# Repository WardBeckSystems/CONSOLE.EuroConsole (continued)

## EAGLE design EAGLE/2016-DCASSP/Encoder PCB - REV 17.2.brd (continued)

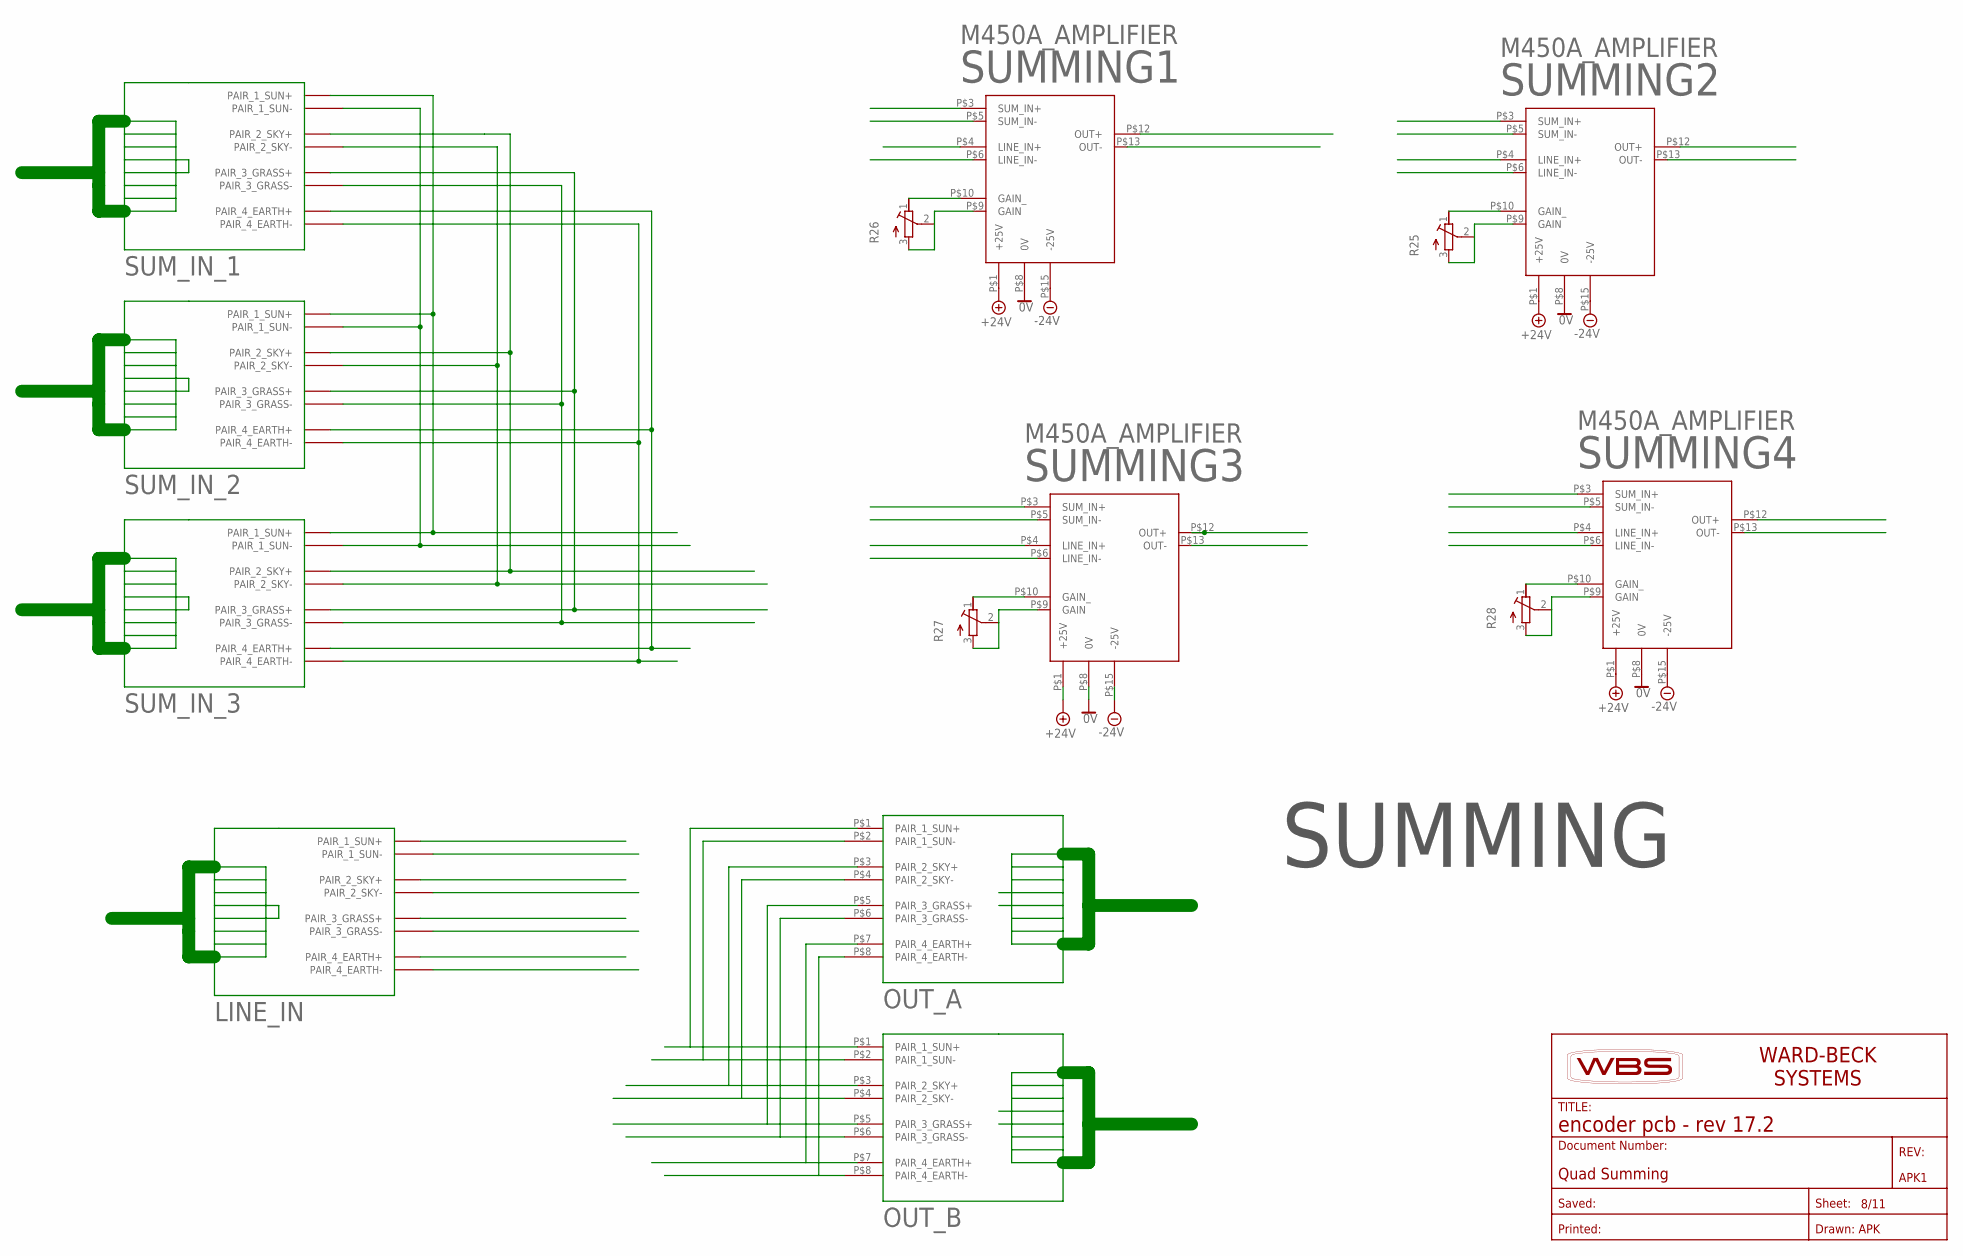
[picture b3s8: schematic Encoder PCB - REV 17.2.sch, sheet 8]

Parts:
APK1: Quad Summing; WBS-FRAME_PCB
LINE_IN: QTP-OUT; PLACEHOLDER
OUT_A: QTP-IN; PLACEHOLDER
OUT_B: QTP-IN; PLACEHOLDER
R25, R26, R27, R28: R-TRIMM43P; RTRIM43P
SUMMING1, SUMMING2, SUMMING3, SUMMING4: M450A_AMPLIFIER
SUM_IN_1, SUM_IN_2, SUM_IN_3: QTP-OUT; PLACEHOLDER

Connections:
0V: SUMMING1.P$8 (0V), SUMMING2.P$8 (0V), SUMMING3.P$8 (0V), SUMMING4.P$8 (0V)
+24V: SUMMING1.P$1 (+25V), SUMMING2.P$1 (+25V), SUMMING3.P$1 (+25V), SUMMING4.P$1 (+25V)
-24V: SUMMING1.P$15 (-25V), SUMMING2.P$15 (-25V), SUMMING3.P$15 (-25V), SUMMING4.P$15 (-25V)
unnamed: SUM_IN_1.P$1 (PAIR_1_SUN+), SUM_IN_1.P$5 (PAIR_3_GRASS+), SUM_IN_1.P$7 (PAIR_4_EARTH+), SUM_IN_2.P$1 (PAIR_1_SUN+), SUM_IN_2.P$3 (PAIR_2_SKY+), SUM_IN_2.P$5 (PAIR_3_GRASS+), SUM_IN_2.P$7 (PAIR_4_EARTH+), SUM_IN_3.P$1 (PAIR_1_SUN+), SUM_IN_3.P$3 (PAIR_2_SKY+), SUM_IN_3.P$5 (PAIR_3_GRASS+), SUM_IN_3.P$7 (PAIR_4_EARTH+)
unnamed: SUM_IN_1.P$2 (PAIR_1_SUN-), SUM_IN_1.P$6 (PAIR_3_GRASS-), SUM_IN_1.P$8 (PAIR_4_EARTH-), SUM_IN_2.P$2 (PAIR_1_SUN-), SUM_IN_2.P$6 (PAIR_3_GRASS-), SUM_IN_2.P$8 (PAIR_4_EARTH-), SUM_IN_3.P$2 (PAIR_1_SUN-), SUM_IN_3.P$4 (PAIR_2_SKY-), SUM_IN_3.P$6 (PAIR_3_GRASS-), SUM_IN_3.P$8 (PAIR_4_EARTH-)
unnamed: SUM_IN_1.P$4 (PAIR_2_SKY-), SUM_IN_2.P$4 (PAIR_2_SKY-)
unnamed: OUT_A.P$8 (PAIR_4_EARTH-), OUT_B.P$8 (PAIR_4_EARTH-)
unnamed: OUT_A.P$4 (PAIR_2_SKY-), OUT_B.P$4 (PAIR_2_SKY-)
unnamed: OUT_A.P$2 (PAIR_1_SUN-), OUT_B.P$2 (PAIR_1_SUN-)
unnamed: OUT_A.P$1 (PAIR_1_SUN+), OUT_B.P$1 (PAIR_1_SUN+)
unnamed: OUT_A.P$3 (PAIR_2_SKY+), OUT_B.P$3 (PAIR_2_SKY+)
unnamed: OUT_A.P$5 (PAIR_3_GRASS+), OUT_B.P$5 (PAIR_3_GRASS+)
unnamed: OUT_A.P$7 (PAIR_4_EARTH+), OUT_B.P$7 (PAIR_4_EARTH+)
unnamed: OUT_A.P$6 (PAIR_3_GRASS-), OUT_B.P$6 (PAIR_3_GRASS-)
unnamed: R25.1 (E), SUMMING2.P$10 (GAIN_)
unnamed: R25.2 (S), R25.3 (A), SUMMING2.P$9 (GAIN)
unnamed: R26.1 (E), SUMMING1.P$10 (GAIN_)
unnamed: R26.2 (S), R26.3 (A), SUMMING1.P$9 (GAIN)
unnamed: R27.1 (E), SUMMING3.P$10 (GAIN_)
unnamed: R27.2 (S), R27.3 (A), SUMMING3.P$9 (GAIN)
unnamed: R28.1 (E), SUMMING4.P$10 (GAIN_)
unnamed: R28.2 (S), R28.3 (A), SUMMING4.P$9 (GAIN)
unnamed: LINE_IN.P$1 (PAIR_1_SUN+), LINE_IN.P$3 (PAIR_2_SKY+), LINE_IN.P$4 (PAIR_2_SKY-), LINE_IN.P$5 (PAIR_3_GRASS+), LINE_IN.P$6 (PAIR_3_GRASS-), LINE_IN.P$7 (PAIR_4_EARTH+), LINE_IN.P$8 (PAIR_4_EARTH-)

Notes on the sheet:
SUMMING

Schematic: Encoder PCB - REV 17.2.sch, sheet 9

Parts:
APK3: VU METER PANEL; WBS-FRAME_PCB
NEOPIXEL1: QTP-IN; PLACEHOLDER
U$7, U$8, U$9, U$10: VU_METER
VU_METER_INPUT: QTP-OUT; PLACEHOLDER

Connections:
unnamed: U$7.P$2, VU_METER_INPUT.P$1 (PAIR_1_SUN+)
unnamed: U$7.P$1, VU_METER_INPUT.P$2 (PAIR_1_SUN-)
unnamed: U$8.P$2, VU_METER_INPUT.P$3 (PAIR_2_SKY+)
unnamed: U$8.P$1, VU_METER_INPUT.P$4 (PAIR_2_SKY-)
unnamed: U$10.P$1, VU_METER_INPUT.P$8 (PAIR_4_EARTH-)
unnamed: U$10.P$2, VU_METER_INPUT.P$7 (PAIR_4_EARTH+)
unnamed: U$9.P$2, VU_METER_INPUT.P$5 (PAIR_3_GRASS+)
unnamed: U$9.P$1, VU_METER_INPUT.P$6 (PAIR_3_GRASS-)
NEO_0V: NEOPIXEL1.P$3 (PAIR_2_SKY+), NEOPIXEL1.P$4 (PAIR_2_SKY-)
NEO_5V: NEOPIXEL1.P$1 (PAIR_1_SUN+), NEOPIXEL1.P$2 (PAIR_1_SUN-)

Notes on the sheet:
VU METERS

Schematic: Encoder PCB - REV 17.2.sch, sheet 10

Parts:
JP1, JP2: PINHD-1X8; 1X08
U3: DS1808Z-050+; SOIC127P600X175-16N
WBS8: DS1882 Adapter; WBS-FRAME_PCB

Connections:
unnamed: JP1.1, U3.1 (GND)
unnamed: JP1.2, U3.2 (A2)
unnamed: JP1.3, U3.3 (A1)
unnamed: JP1.4, U3.4 (VB)
unnamed: JP1.5, U3.5 (A0)
unnamed: JP1.6, U3.6 (W0)
unnamed: JP1.7, U3.7 (L0)
unnamed: JP1.8, U3.8 (H0)
unnamed: JP2.1, U3.9 (L1)
unnamed: JP2.2, U3.10 (H1)
unnamed: JP2.3, U3.11 (W)
unnamed: JP2.4, U3.12 (~CE)
unnamed: JP2.5, U3.13 (SDA)
unnamed: JP2.6, U3.14 (SCL)
unnamed: JP2.7, U3.15 (VCC)
unnamed: JP2.8, U3.16 (VDD)

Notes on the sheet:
DCP-Socket

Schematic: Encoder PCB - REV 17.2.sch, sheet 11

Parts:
BNC2: 1-227161-0; AMP_227161
C14: 100n/50v; C0805
EURO-BLOCK_2: CON-PHOENIX_RIGHT_ANGLE_3.81; CON-PHOENIX_MC1.5/3-G-3.81
G2: LSP10
GND-2: SJ
GROUND_POST: 22-23-2031
PAN_CON_2: 22-23-2031
QTP1, QTP2: CON-QTP; ASSMAN-RJ45
QTP_CENTER: CON-QTP; ASSMAN-RJ45
R201: 0R; R0805W
R202, R204: 37R5; R0805W
R203: 75R; R0805W
REARTH+: 0R; R0805W
REARTH-: 0R; R0805W
RGRASS+: 0R; R0805W
RGRASS-: 0R; R0805W
RSKY+: 0R; R0805W
RSKY-: 0R; R0805W
RSUN+: 0R; R0805W
RSUN-: 0R; R0805W
SJ_2: SJ
T2: XFMR_SCHOTT_61454; SCHOTT_61454
WBS9: QTP-BAC; WBS-FRAME_PCB
X2: 2514-; PAK100/2500-14
XLR2: CON-XLR-NEUTRIK_A_BISEXUAL; CON_NEUTRIK_A_BISEXUAL_H

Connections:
CH1+1: QTP1.P1+ (PAIR+1_SUN), QTP2.P1+ (PAIR+1_SUN), QTP_CENTER.P1+ (PAIR+1_SUN), RSUN+.1
CH1-1: QTP1.P1- (PAIR-1), QTP2.P1- (PAIR-1), QTP_CENTER.P1- (PAIR-1), RSUN-.1
CH2+1: EURO-BLOCK_2.+, PAN_CON_2.1, QTP1.P2+ (PAIR+2_SKY), QTP2.P2+ (PAIR+2_SKY), QTP_CENTER.P2+ (PAIR+2_SKY), RSKY+.1, T2.P5, XLR2.F2 (F2+), XLR2.M2 (M2+)
CH2-1: EURO-BLOCK_2.-, PAN_CON_2.2, QTP1.P2- (PAIR-2), QTP2.P2- (PAIR-2), QTP_CENTER.P2- (PAIR-2), RSKY-.1, T2.P8, XLR2.SHARED3 (S3-)
CH3+1: QTP1.P3+ (PAIR+3_GRASS), QTP2.P3+ (PAIR+3_GRASS), QTP_CENTER.P3+ (PAIR+3_GRASS), RGRASS+.1
CH3-1: QTP1.P3- (PAIR-3), QTP2.P3- (PAIR-3), QTP_CENTER.P3- (PAIR-3), RGRASS-.1
CH4+1: QTP1.P4+ (PAIR+4_EARTH), QTP2.P4+ (PAIR+4_EARTH), QTP_CENTER.P4+ (PAIR+4_EARTH), REARTH+.1
CH4-1: QTP1.P4- (PAIR-4), QTP2.P4- (PAIR-4), QTP_CENTER.P4- (PAIR-4), REARTH-.1
GND: GND-2.2, GROUND_POST.1, GROUND_POST.2, GROUND_POST.3, QTP1.P$9 (GROUND), QTP1.P$10 (GROUND), QTP1.P$11 (GROUND), QTP1.P$12 (GROUND), QTP2.P$9 (GROUND), QTP2.P$10 (GROUND), QTP2.P$11 (GROUND), QTP2.P$12 (GROUND), QTP_CENTER.P$9 (GROUND), QTP_CENTER.P$10 (GROUND), QTP_CENTER.P$11 (GROUND), QTP_CENTER.P$12 (GROUND), X2.3, X2.6, X2.9, X2.12; also elsewhere on the board
GND_PIN1_2: BNC2.2, C14.1, EURO-BLOCK_2.S, G2.MP, GND-2.1, PAN_CON_2.3, R203.2, T2.P4, T2.P6, XLR2.CHASSIS (GROUND), XLR2.F1, XLR2.GROUND, XLR2.M1
unnamed: R201.2, R204.2, T2.P1
unnamed: R202.2, R204.1, SJ_2.1
unnamed: BNC2.1, R201.1, R202.1
unnamed: C14.2, T2.P7
unnamed: R203.1, SJ_2.2
unnamed: RSUN+.2, X2.10
unnamed: REARTH-.2, X2.2
unnamed: REARTH+.2, X2.1
unnamed: RGRASS-.2, X2.5
unnamed: RGRASS+.2, X2.4
unnamed: RSKY-.2, X2.8
unnamed: RSKY+.2, X2.7
unnamed: RSUN-.2, X2.11

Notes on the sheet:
QTP-XLR

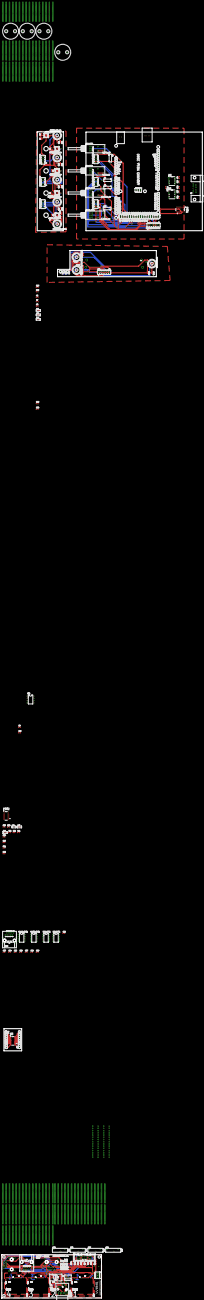
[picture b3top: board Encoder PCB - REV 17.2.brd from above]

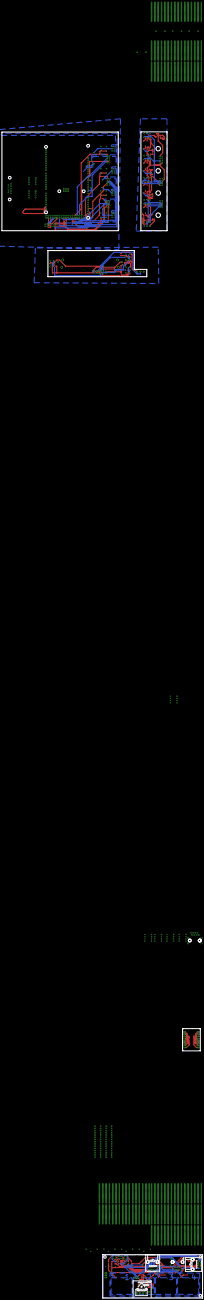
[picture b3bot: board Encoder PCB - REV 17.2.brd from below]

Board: 2 copper layers, 229.9 x 1336.6 mm, 214 parts (3 on the bottom side), 158 nets.

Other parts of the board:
U$5: C1-4-150731-094535
U$6: C2-5-150731-094535
U$11: C3-6-150731-094535
U$12: C4-7-150731-094535
U$13: GND_1-8-150731-094535
U$14: GND_2-9-150731-094535
U$15: GND_3-10-150731-094535
U$16: GND_4-11-150731-094535
U$17: GROUND_P-12-150731-094535
U$18: R101-17-150731-094535
U$19: R102-18-150731-094535
U$20: R103-19-150731-094535
U$21: R104-20-150731-094535
U$22: R201-21-150731-094535
U$23: R202-22-150731-094535
U$24: R203-23-150731-094535
U$25: R204-24-150731-094535
U$26: R301-25-150731-094535
U$27: R302-26-150731-094535
U$28: R303-27-150731-094535
U$29: R304-28-150731-094535
U$30: R401-29-150731-094535
U$31: R402-30-150731-094535
U$32: R403-31-150731-094535
U$33: R404-32-150731-094535
U$34: REARTH_-33-150731-094535
U$35: REARTH_-34-150731-094535
U$36: RGRASS_-35-150731-094535
U$37: RGRASS_-36-150731-094535
U$38: RSKY_-37-150731-094535
U$39: RSKY_-38-150731-094535
U$40: RSUN_-39-150731-094535
U$41: RSUN_-40-150731-094535
U$42: SJ_1-41-150731-094535
U$43: SJ_2-42-150731-094536
U$44: SJ_3-43-150731-094536
U$45: SJ_4-44-150731-094536
U$46: GND_PIN1_1; T1-45-150731-094536
U$47: GND_PIN1_2; T2-46-150731-094536
U$48: gnd; T3-47-150731-094536
U$49: gnd; T4-48-150731-094536

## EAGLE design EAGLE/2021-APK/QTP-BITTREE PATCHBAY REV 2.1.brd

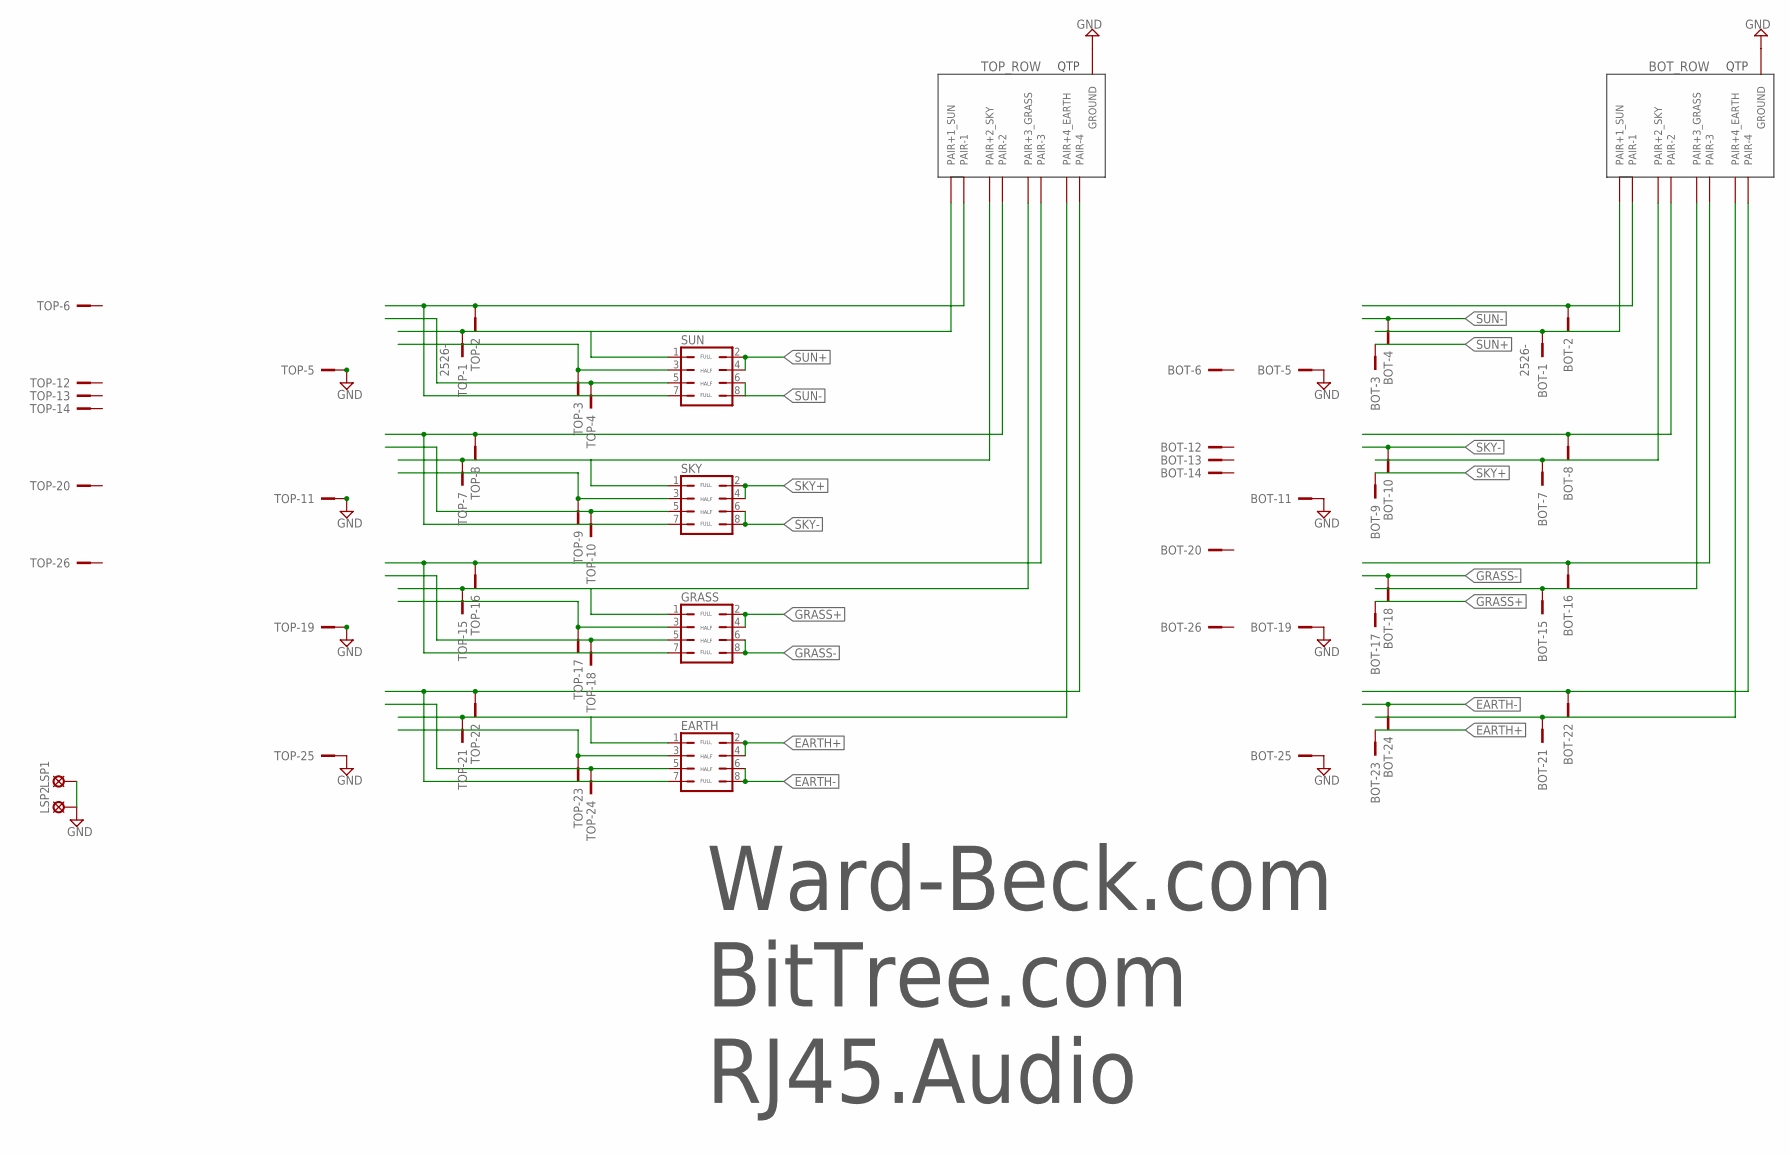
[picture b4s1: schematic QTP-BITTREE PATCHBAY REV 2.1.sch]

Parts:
BOT: 2526-; PAK100/2500-26
BOT_ROW: CON-QTP_VERT; ASSMAN-RJ45_VERT
EARTH: JP4Q
GRASS: JP4Q
LSP1, LSP2: LSP13
SKY: JP4Q
SUN: JP4Q
TOP: 2526-; PAK100/2500-26
TOP_ROW: CON-QTP_VERT; ASSMAN-RJ45_VERT

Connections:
EARTH+: BOT.23, EARTH.2, EARTH.4
EARTH-: BOT.24, EARTH.6, EARTH.8
GND: BOT.5, BOT.11, BOT.19, BOT.25, BOT_ROW.P$9 (GROUND), BOT_ROW.P$10 (GROUND), BOT_ROW.P$11 (GROUND), BOT_ROW.P$12 (GROUND), LSP1.MP, LSP2.MP, TOP.5, TOP.11, TOP.19, TOP.25, TOP_ROW.P$9 (GROUND), TOP_ROW.P$10 (GROUND), TOP_ROW.P$11 (GROUND), TOP_ROW.P$12 (GROUND)
GRASS+: BOT.17, GRASS.2, GRASS.4
GRASS-: BOT.18, GRASS.6, GRASS.8
unnamed: SUN.7, TOP.2, TOP_ROW.P$1 (PAIR-1)
unnamed: SKY.1, TOP.7, TOP_ROW.P$4 (PAIR+2_SKY)
unnamed: BOT.1, BOT_ROW.P$2 (PAIR+1_SUN)
unnamed: GRASS.1, TOP.15, TOP_ROW.P$6 (PAIR+3_GRASS)
unnamed: BOT.2, BOT_ROW.P$1 (PAIR-1)
unnamed: EARTH.1, TOP.21, TOP_ROW.P$8 (PAIR+4_EARTH)
unnamed: SUN.3, TOP.3
unnamed: SUN.5, TOP.4
unnamed: BOT.7, BOT_ROW.P$4 (PAIR+2_SKY)
unnamed: SKY.7, TOP.8, TOP_ROW.P$5 (PAIR-2)
unnamed: SKY.3, TOP.9
unnamed: SKY.5, TOP.10
unnamed: BOT.15, BOT_ROW.P$6 (PAIR+3_GRASS)
unnamed: GRASS.7, TOP.16, TOP_ROW.P$3 (PAIR-3)
unnamed: GRASS.3, TOP.17
unnamed: GRASS.5, TOP.18
unnamed: BOT.21, BOT_ROW.P$8 (PAIR+4_EARTH)
unnamed: EARTH.7, TOP.22, TOP_ROW.P$7 (PAIR-4)
unnamed: EARTH.3, TOP.23
unnamed: EARTH.5, TOP.24
unnamed: BOT.8, BOT_ROW.P$5 (PAIR-2)
unnamed: BOT.16, BOT_ROW.P$3 (PAIR-3)
unnamed: BOT.22, BOT_ROW.P$7 (PAIR-4)
SKY+: BOT.9, SKY.2, SKY.4
SKY-: BOT.10, SKY.6, SKY.8
SUN+: BOT.3, SUN.2, SUN.4
SUN-: BOT.4, SUN.6, SUN.8
TOP-P1: SUN.1, TOP.1, TOP_ROW.P$2 (PAIR+1_SUN)

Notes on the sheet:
FULL
HALF
Ward-Beck.com
BitTree.com RJ45.Audio

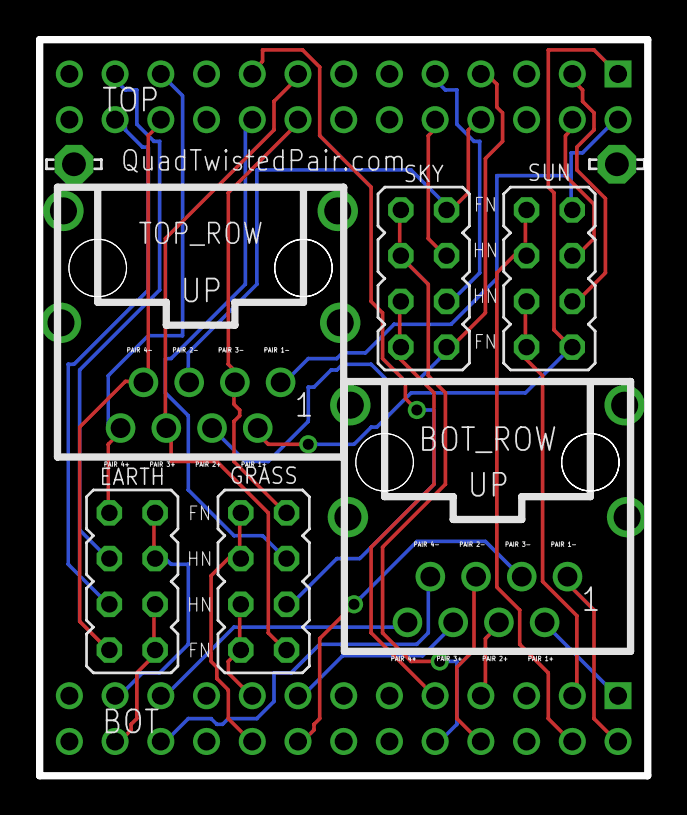
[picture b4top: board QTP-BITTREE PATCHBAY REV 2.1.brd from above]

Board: 2 copper layers, 33.8 x 40.9 mm, 10 parts (0 on the bottom side), 33 nets.

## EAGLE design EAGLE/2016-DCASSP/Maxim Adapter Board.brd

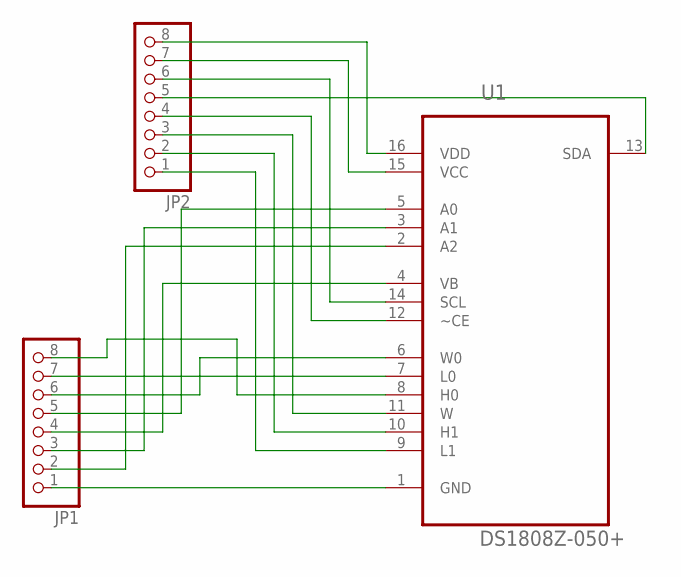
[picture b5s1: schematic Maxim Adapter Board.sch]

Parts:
JP1, JP2: PINHD-1X8; 1X08
U1: DS1808Z-050+; SOIC127P600X175-16N

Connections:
unnamed: JP1.1, U1.1 (GND)
unnamed: JP1.2, U1.2 (A2)
unnamed: JP1.3, U1.3 (A1)
unnamed: JP1.4, U1.4 (VB)
unnamed: JP1.5, U1.5 (A0)
unnamed: JP1.6, U1.6 (W0)
unnamed: JP1.7, U1.7 (L0)
unnamed: JP1.8, U1.8 (H0)
unnamed: JP2.1, U1.9 (L1)
unnamed: JP2.2, U1.10 (H1)
unnamed: JP2.3, U1.11 (W)
unnamed: JP2.4, U1.12 (~CE)
unnamed: JP2.5, U1.13 (SDA)
unnamed: JP2.6, U1.14 (SCL)
unnamed: JP2.7, U1.15 (VCC)
unnamed: JP2.8, U1.16 (VDD)

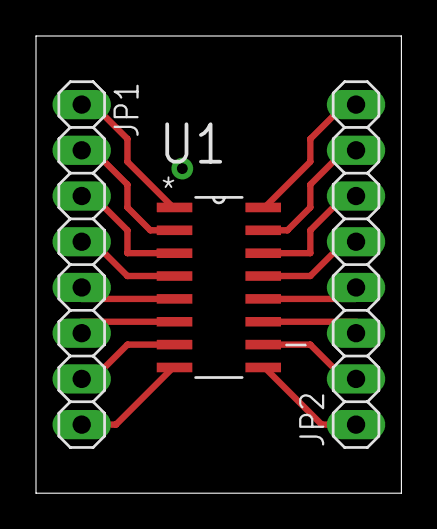
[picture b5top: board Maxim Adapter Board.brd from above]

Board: 2 copper layers, 20.3 x 25.4 mm, 3 parts (0 on the bottom side), 16 nets.

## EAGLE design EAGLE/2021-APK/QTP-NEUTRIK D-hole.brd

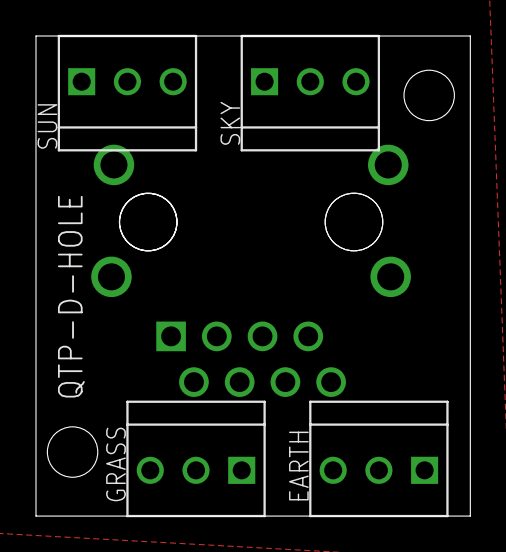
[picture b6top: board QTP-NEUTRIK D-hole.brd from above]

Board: 2 copper layers, 24.1 x 26.7 mm, 5 parts (1 on the bottom side), 9 nets, no tracks yet.

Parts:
EARTH: CON-WBS-LOCKING-0.1-3
GRASS: CON-WBS-LOCKING-0.1-3
SKY: CON-WBS-LOCKING-0.1-3
SUN: CON-WBS-LOCKING-0.1-3
U$1: CON-QTP_VERT; ASSMAN-RJ45_VERT

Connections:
GND: EARTH.P$3, GRASS.P$3, SKY.P$3, SUN.P$3, U$1.P$9, U$1.P$10, U$1.P$11, U$1.P$12
unnamed: SUN.P$1, U$1.P$2
unnamed: SUN.P$2, U$1.P$1
unnamed: SKY.P$1, U$1.P$4
unnamed: GRASS.P$1, U$1.P$6
unnamed: GRASS.P$2, U$1.P$3
unnamed: EARTH.P$1, U$1.P$8
unnamed: EARTH.P$2, U$1.P$7
SUN_N: SKY.P$2, U$1.P$5

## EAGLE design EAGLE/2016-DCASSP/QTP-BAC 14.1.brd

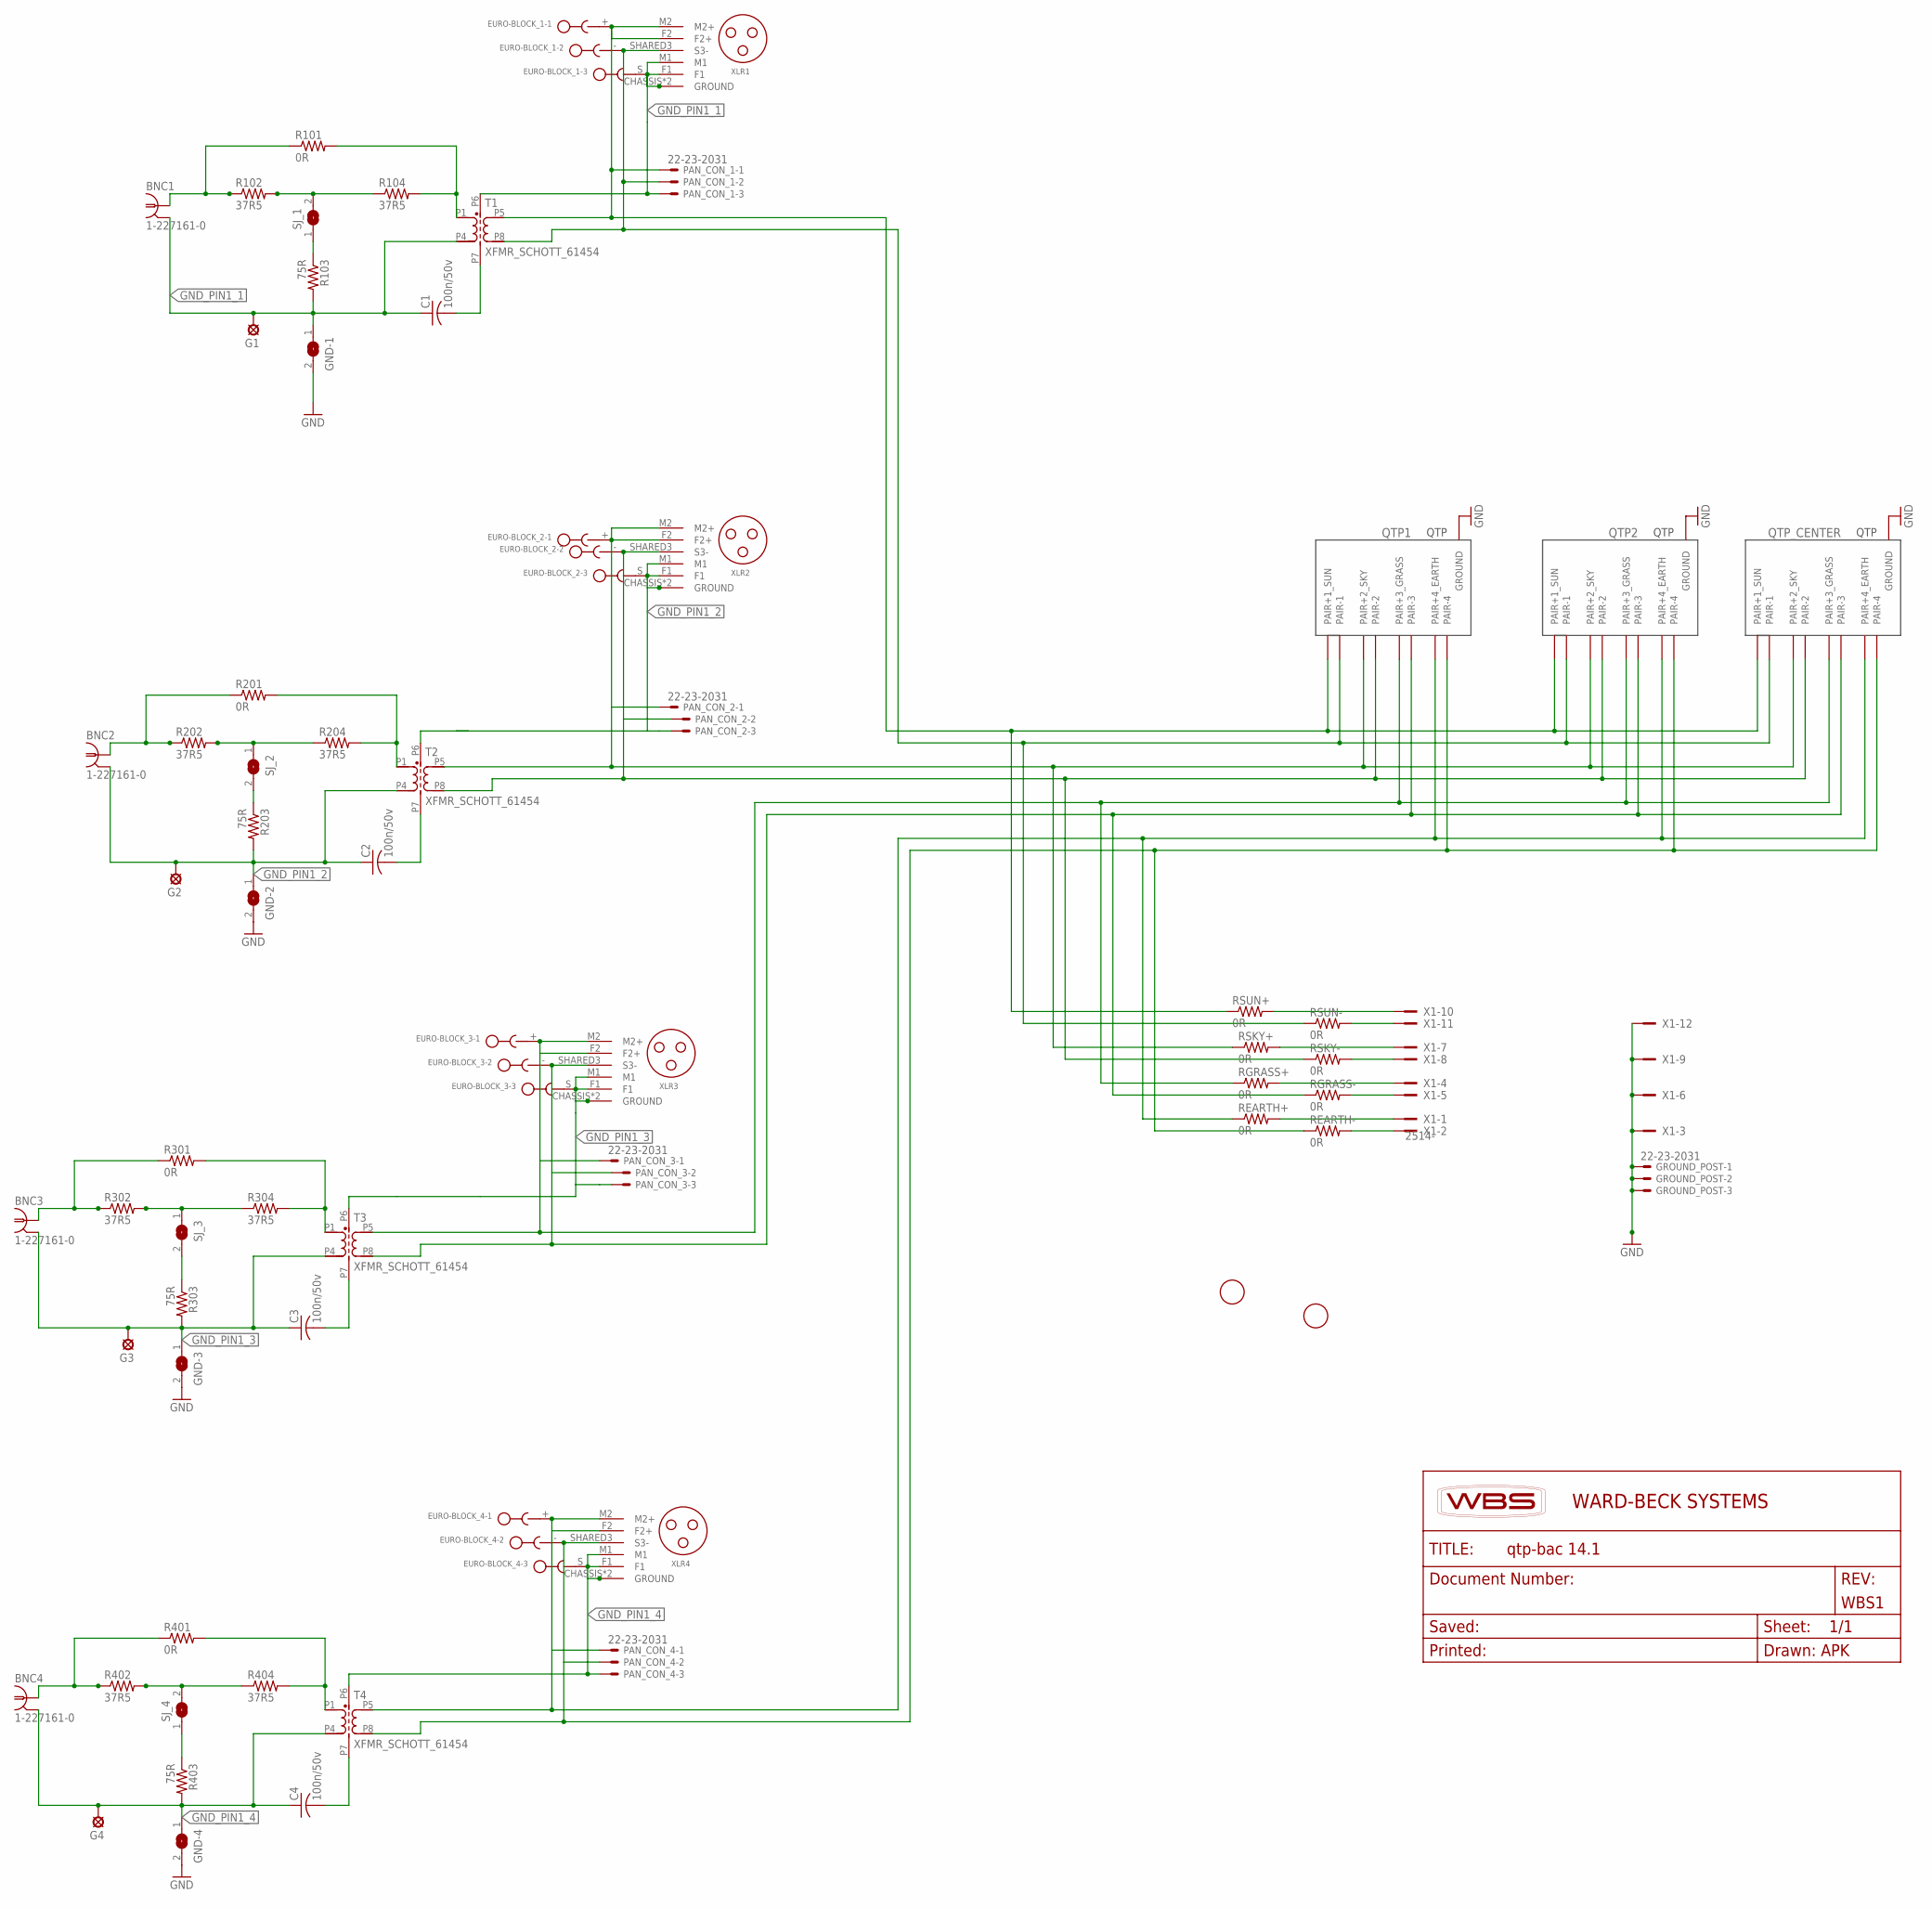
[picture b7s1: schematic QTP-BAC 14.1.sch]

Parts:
BNC1, BNC2, BNC3, BNC4: 1-227161-0; AMP_227161
C1, C2, C3, C4: 100n/50v; C0805
EURO-BLOCK_1, EURO-BLOCK_2, EURO-BLOCK_3, EURO-BLOCK_4: CON-PHOENIX_RIGHT_ANGLE_3.81; CON-PHOENIX_MC1.5/3-G-3.81
G1, G2, G3, G4: LSP10
GND-1, GND-2, GND-3, GND-4: SJ
GROUND_POST: 22-23-2031
PAN_CON_1, PAN_CON_2, PAN_CON_3, PAN_CON_4: 22-23-2031
QTP1, QTP2: CON-QTP; ASSMAN-RJ45
QTP_CENTER: CON-QTP; ASSMAN-RJ45
R101, R201, R301, R401: 0R; R0805W
R102, R104, R202, R204, R302, R304, R402, R404: 37R5; R0805W
R103, R203, R303, R403: 75R; R0805W
REARTH+: 0R; R0805W
REARTH-: 0R; R0805W
RGRASS+: 0R; R0805W
RGRASS-: 0R; R0805W
RSKY+: 0R; R0805W
RSKY-: 0R; R0805W
RSUN+: 0R; R0805W
RSUN-: 0R; R0805W
SJ_1, SJ_2, SJ_3, SJ_4: SJ
T1, T2, T3, T4: XFMR_SCHOTT_61454; SCHOTT_61454
U$1, U$2: FIDUCIAL; FIDUCIAL_1MM
WBS1: WBS-DOCUMENT_INFO_FRAME; WBS-FRAME_PCB
X1: 2514-; PAK100/2500-14
XLR1, XLR2, XLR3, XLR4: CON-XLR-NEUTRIK_A_BISEXUAL; CON_NEUTRIK_A_BISEXUAL_H

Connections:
CH1+1: EURO-BLOCK_1.+, PAN_CON_1.1, QTP1.P1+ (PAIR+1_SUN), QTP2.P1+ (PAIR+1_SUN), QTP_CENTER.P1+ (PAIR+1_SUN), RSUN+.1, T1.P5, XLR1.F2 (F2+), XLR1.M2 (M2+)
CH1-1: EURO-BLOCK_1.-, PAN_CON_1.2, QTP1.P1- (PAIR-1), QTP2.P1- (PAIR-1), QTP_CENTER.P1- (PAIR-1), RSUN-.1, T1.P8, XLR1.SHARED3 (S3-)
CH2+1: EURO-BLOCK_2.+, PAN_CON_2.1, QTP1.P2+ (PAIR+2_SKY), QTP2.P2+ (PAIR+2_SKY), QTP_CENTER.P2+ (PAIR+2_SKY), RSKY+.1, T2.P5, XLR2.F2 (F2+), XLR2.M2 (M2+)
CH2-1: EURO-BLOCK_2.-, PAN_CON_2.2, QTP1.P2- (PAIR-2), QTP2.P2- (PAIR-2), QTP_CENTER.P2- (PAIR-2), RSKY-.1, T2.P8, XLR2.SHARED3 (S3-)
CH3+1: EURO-BLOCK_3.+, PAN_CON_3.1, QTP1.P3+ (PAIR+3_GRASS), QTP2.P3+ (PAIR+3_GRASS), QTP_CENTER.P3+ (PAIR+3_GRASS), RGRASS+.1, T3.P5, XLR3.F2 (F2+), XLR3.M2 (M2+)
CH3-1: EURO-BLOCK_3.-, PAN_CON_3.2, QTP1.P3- (PAIR-3), QTP2.P3- (PAIR-3), QTP_CENTER.P3- (PAIR-3), RGRASS-.1, T3.P8, XLR3.SHARED3 (S3-)
CH4+1: EURO-BLOCK_4.+, PAN_CON_4.1, QTP1.P4+ (PAIR+4_EARTH), QTP2.P4+ (PAIR+4_EARTH), QTP_CENTER.P4+ (PAIR+4_EARTH), REARTH+.1, T4.P5, XLR4.F2 (F2+), XLR4.M2 (M2+)
CH4-1: EURO-BLOCK_4.-, PAN_CON_4.2, QTP1.P4- (PAIR-4), QTP2.P4- (PAIR-4), QTP_CENTER.P4- (PAIR-4), REARTH-.1, T4.P8, XLR4.SHARED3 (S3-)
GND: GND-1.2, GND-2.2, GND-3.2, GND-4.2, GROUND_POST.1, GROUND_POST.2, GROUND_POST.3, QTP1.P$9 (GROUND), QTP1.P$10 (GROUND), QTP1.P$11 (GROUND), QTP1.P$12 (GROUND), QTP2.P$9 (GROUND), QTP2.P$10 (GROUND), QTP2.P$11 (GROUND), QTP2.P$12 (GROUND), QTP_CENTER.P$9 (GROUND), QTP_CENTER.P$10 (GROUND), QTP_CENTER.P$11 (GROUND), QTP_CENTER.P$12 (GROUND), X1.3, X1.6, X1.9, X1.12
GND_PIN1_1: BNC1.2, C1.1, EURO-BLOCK_1.S, G1.MP, GND-1.1, PAN_CON_1.3, R103.2, T1.P4, T1.P6, XLR1.CHASSIS (GROUND), XLR1.F1, XLR1.GROUND, XLR1.M1
GND_PIN1_2: BNC2.2, C2.1, EURO-BLOCK_2.S, G2.MP, GND-2.1, PAN_CON_2.3, R203.2, T2.P4, T2.P6, XLR2.CHASSIS (GROUND), XLR2.F1, XLR2.GROUND, XLR2.M1
GND_PIN1_3: BNC3.2, C3.1, EURO-BLOCK_3.S, G3.MP, GND-3.1, PAN_CON_3.3, R303.2, T3.P4, T3.P6, XLR3.CHASSIS (GROUND), XLR3.F1, XLR3.GROUND, XLR3.M1
GND_PIN1_4: BNC4.2, C4.1, EURO-BLOCK_4.S, G4.MP, GND-4.1, PAN_CON_4.3, R403.2, T4.P4, T4.P6, XLR4.CHASSIS (GROUND), XLR4.F1, XLR4.GROUND, XLR4.M1
unnamed: R102.2, R104.1, SJ_1.2
unnamed: C1.2, T1.P7
unnamed: R101.2, R104.2, T1.P1
unnamed: R103.1, SJ_1.1
unnamed: BNC1.1, R101.1, R102.1
unnamed: R203.1, SJ_2.2
unnamed: R303.1, SJ_3.2
unnamed: R201.2, R204.2, T2.P1
unnamed: R202.2, R204.1, SJ_2.1
unnamed: BNC2.1, R201.1, R202.1
unnamed: C2.2, T2.P7
unnamed: R403.1, SJ_4.1
unnamed: R301.2, R304.2, T3.P1
unnamed: R302.2, R304.1, SJ_3.1
unnamed: BNC3.1, R301.1, R302.1
unnamed: C3.2, T3.P7
unnamed: R401.2, R404.2, T4.P1
unnamed: R402.2, R404.1, SJ_4.2
unnamed: BNC4.1, R401.1, R402.1
unnamed: C4.2, T4.P7
unnamed: REARTH-.2, X1.2
unnamed: REARTH+.2, X1.1
unnamed: RGRASS-.2, X1.5
unnamed: RSUN+.2, X1.10
unnamed: RGRASS+.2, X1.4
unnamed: RSKY-.2, X1.8
unnamed: RSKY+.2, X1.7
unnamed: RSUN-.2, X1.11

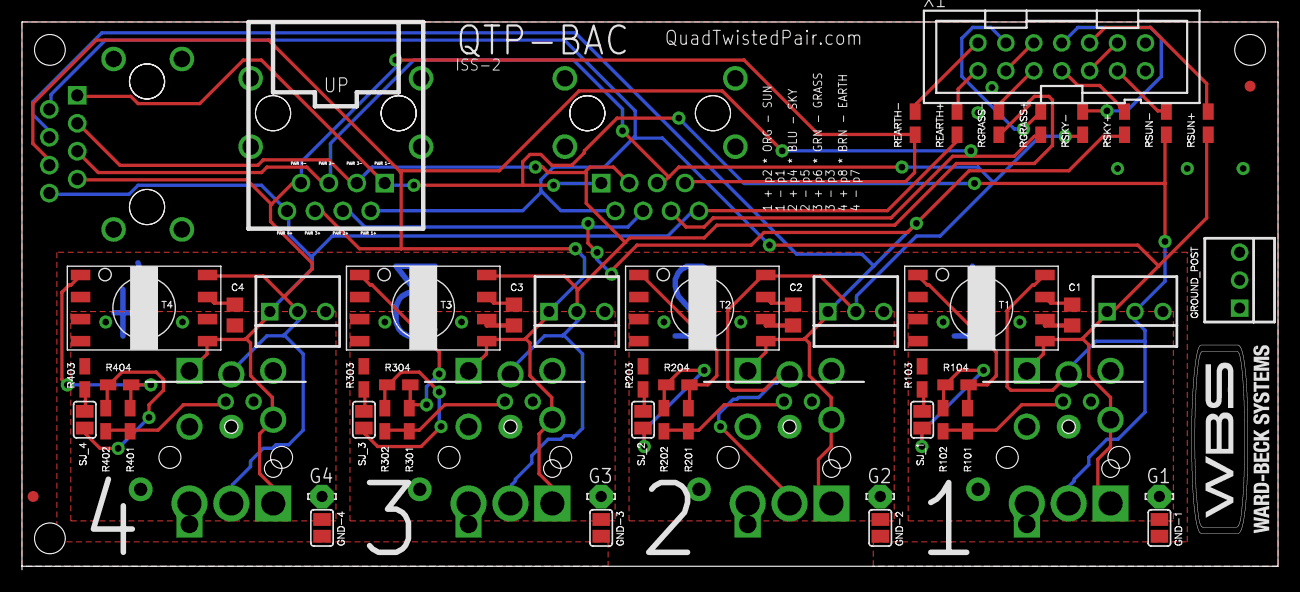
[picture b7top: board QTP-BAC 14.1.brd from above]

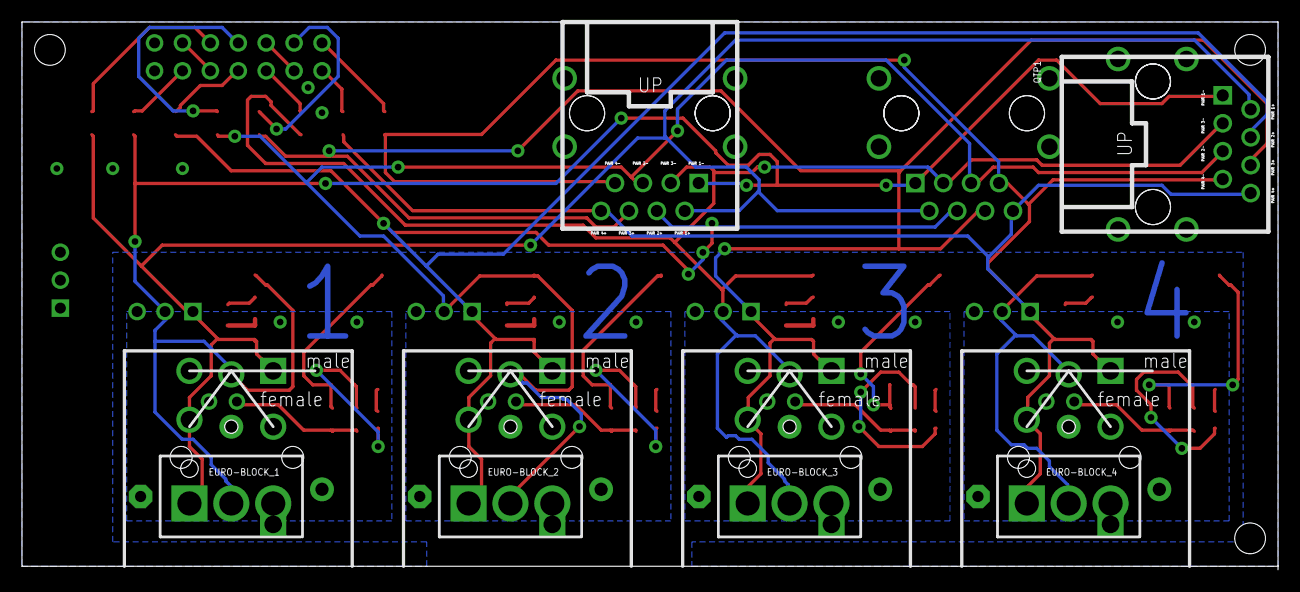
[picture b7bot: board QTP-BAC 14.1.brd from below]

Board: 2 copper layers, 114.3 x 49.5 mm, 109 parts (6 on the bottom side), 41 nets.

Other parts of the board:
U$4: C1-4-150731-094535
U$5: C2-5-150731-094535
U$6: C3-6-150731-094535
U$7: C4-7-150731-094535
U$9: GND_1-8-150731-094535
U$10: GND_2-9-150731-094535
U$11: GND_3-10-150731-094535
U$12: GND_4-11-150731-094535
U$13: GROUND_P-12-150731-094535
U$18: R101-17-150731-094535
U$19: R102-18-150731-094535
U$20: R103-19-150731-094535
U$21: R104-20-150731-094535
U$22: R201-21-150731-094535
U$23: R202-22-150731-094535
U$24: R203-23-150731-094535
U$25: R204-24-150731-094535
U$26: R301-25-150731-094535
U$27: R302-26-150731-094535
U$28: R303-27-150731-094535
U$29: R304-28-150731-094535
U$30: R401-29-150731-094535
U$31: R402-30-150731-094535
U$32: R403-31-150731-094535
U$33: R404-32-150731-094535
U$34: REARTH_-33-150731-094535
U$35: REARTH_-34-150731-094535
U$36: RGRASS_-35-150731-094535
U$37: RGRASS_-36-150731-094535
U$38: RSKY_-37-150731-094535
U$39: RSKY_-38-150731-094535
U$40: RSUN_-39-150731-094535
U$41: RSUN_-40-150731-094535
U$42: SJ_1-41-150731-094535
U$43: SJ_2-42-150731-094536
U$44: SJ_3-43-150731-094536
U$45: SJ_4-44-150731-094536
U$46: GND_PIN1_1; T1-45-150731-094536
U$47: GND_PIN1_2; T2-46-150731-094536
U$48: gnd; T3-47-150731-094536
U$49: gnd; T4-48-150731-094536

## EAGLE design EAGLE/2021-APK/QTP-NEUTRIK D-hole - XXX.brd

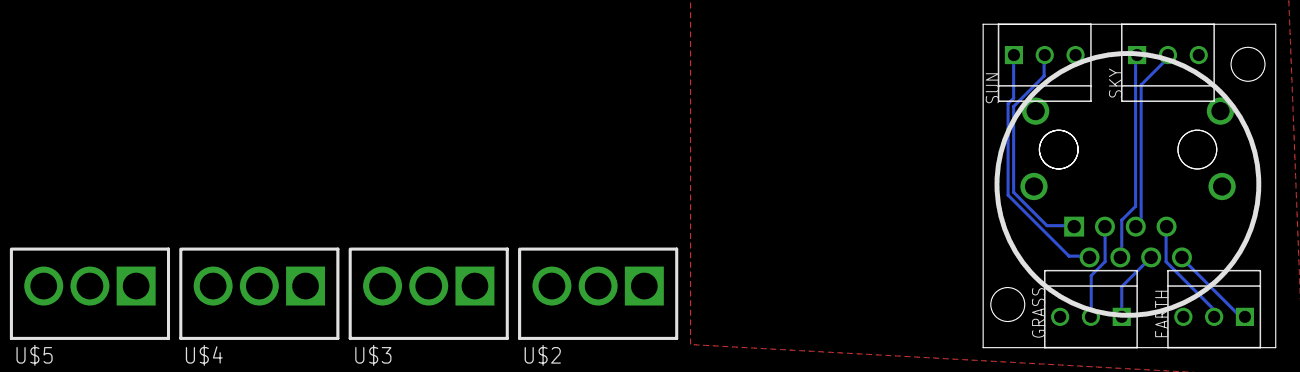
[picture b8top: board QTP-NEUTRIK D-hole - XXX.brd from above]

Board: 2 copper layers, 24.1 x 26.7 mm, 9 parts (1 on the bottom side), 9 nets.

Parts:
EARTH: CON-WBS-LOCKING-0.1-3
GRASS: CON-WBS-LOCKING-0.1-3
SKY: CON-WBS-LOCKING-0.1-3
SUN: CON-WBS-LOCKING-0.1-3
U$1: CON-QTP_VERT; ASSMAN-RJ45_VERT
U$2, U$3, U$4, U$5: CON-PHOENIX_RIGHT_ANGLE_3.81; CON-PHOENIX_MC1.5/3-G-3.81

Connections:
GND: EARTH.P$3, GRASS.P$3, SKY.P$3, SUN.P$3, U$1.P$9, U$1.P$10, U$1.P$11, U$1.P$12, U$2.S, U$3.S, U$4.S, U$5.S
unnamed: SUN.P$1, U$1.P$2, U$2.+
unnamed: SUN.P$2, U$1.P$1, U$2.-
unnamed: SKY.P$1, U$1.P$4, U$3.+
unnamed: GRASS.P$1, U$1.P$6, U$4.+
unnamed: GRASS.P$2, U$1.P$3, U$4.-
unnamed: EARTH.P$1, U$1.P$8, U$5.+
unnamed: EARTH.P$2, U$1.P$7, U$5.-
SUN_N: SKY.P$2, U$1.P$5, U$3.-
